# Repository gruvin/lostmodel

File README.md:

# Open Source RC Lost Model Alarm 
* Two modes -- Normal (manual switch) or Inactivity
* Modes programmable from TX 
* Resonated PIEZO
* LOUD!

Hardware design created in free, open source KiCAD EDA suite.

Employs ATmega88PA (5x5mm MLF) to intelligently drive a quartz piezo via autotransformer at 2.8KHz resonant frequency. This gives air and ear peircingly, LOUD output. Piezo and transformer taken from cheap personal alarm.

The circuit board is 16x33mm and the piezo is 28mm diameter and 3mm thick, including resonance chamber. The autotransformer (11mm height) can be mounted either on the top or bottom of the PCB or off board, if needed for space.

There are three status LEDs. Green, Blue and Red. They do, umm, stuff.

Programming and status tones are emitted (at lower, close range tolerable volume levels!) using Morse code, which I consider better than counting beeps for programming and status reporting.

The alarm can work in either Normal or Inactivity mode.

In Inactivity mode, ear peircing noise is made when there has been no receiver channel activity for a short while. Useful for cases where a dedicated RC channel is not available. Connect to aileron or elevator channel, for example.

Normal mode uses a dedicated receiver channel as a simple on/off switch. (Greater than or lower than mid point.)

## KiCAD v4 PCB Render

Autotransformer and off-board quartz piezo not shown.

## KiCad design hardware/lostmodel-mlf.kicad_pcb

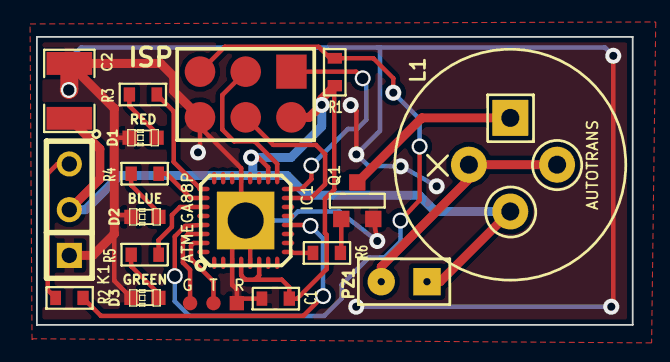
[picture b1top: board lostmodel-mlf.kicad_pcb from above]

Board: 2 copper layers, 33.1 x 16.0 mm, 18 parts (0 on the bottom side), 20 nets.

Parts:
C1: 0u1; SM0603_GRUVIN
C2: 22u; SM1210_GRUVIN_POL
D1: RED; LED-0603
D2: BLUE; LED-0603
D3: GREEN; LED-0603
IC1: ATMEGA88P; MLF-32_2mmVIA_SINK
K1: CONN_3; SIL-3
K2: G T R; TP-3
L1: AUTOTRANS; TRI-3
P1: ISP; PIN_ARRAY_3x2_GRUVIN
PZ1: PIEZO; PIN_ARRAY_2X1
Q1: BC847C; SOT23-BCE
R1: 5K6; SM0603_GRUVIN
R2: 200; SM0603_GRUVIN
R3, R6: 1K; SM0603_GRUVIN
R4: 3K9; SM0603_GRUVIN
R5: 1K5; SM0603_GRUVIN

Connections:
+5V: C1.1, C2.1, IC1.4, IC1.6, IC1.18, K1.2, L1.2, P1.2, PZ1.1, R1.1
/LED01: IC1.25, R3.2
/LED02: IC1.26, R4.2
/LED03: IC1.27, R5.2
/MISO: IC1.16, P1.1
/MOSI: IC1.15, P1.4
/RESET: IC1.29, P1.5, R1.2
/SCK: IC1.17, P1.3
/SIG: K1.3, R2.2
GND: C1.2, C2.2, D1.2, D2.2, D3.2, IC1.0, IC1.3, IC1.5, IC1.21, K1.1, K2.1, P1.6, Q1.2
unnamed: D1.1, R3.1
unnamed: D2.1, R4.1
unnamed: D3.1, R5.1
unnamed: IC1.9, R6.2
unnamed: IC1.12, R2.1
unnamed: IC1.30, K2.3
unnamed: IC1.31, K2.2
unnamed: L1.1, Q1.3
unnamed: L1.3, PZ1.2
unnamed: Q1.1, R6.1

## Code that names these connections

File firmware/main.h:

#ifndef _MAIN_H
#define _MAIN_H

#define DEBUG 1

// CW dit length (arbitrary units)
#define DITLENGTH 8 // arbitrary while morseStateMachine is just part of the main loop

// TODO: prototype version. Pins changed for production version ...
//       These are NOT the pins specified in the production electronic schematic
#define SIG_INP   PIND
#define SIG_PORT  PORTD
#define SIG_DDR   DDRD
#define SIG_BIT   3 // D-

#define PIEZO_PORT PORTD
#define PIEZO_DDR  DDRD
#define PIEZO_BIT  5 // LED01

#define LED1_PORT PORTC
#define LED1_DDR  DDRC
#define LED1_BIT  3 // LED05 (not used in prototype)

#define LED2_PORT PORTD
#define LED2_DDR  DDRD
#define LED2_BIT  4 // LED02

#define LED3_PORT PORTC
#define LED3_DDR  DDRC
#define LED3_BIT  5 // LED03

#define LED_ON(a) LED ## a ## _PORT |= (1<<LED ## a ## _BIT)
#define LED_OFF(a) LED ## a ## _PORT &= ~(1<<LED ## a ## _BIT)

#define MIDPOINT 1400 // timing loop should be exactly 10 clock cycles => 1200 loops for 1.5ms. 1400 works in practice. *shrug*

// PWM piezo output volume
#ifdef DEBUG
#define PWM_DUTY_CYCLE 3
#else
#define PWM_DUTY_CYCLE 27
#endif
#define PWM_DUTY_CYCLE_QUIET 2

#define true (-1)
#define false 0

// Run Modes
#define NORMAL 0
#define INACTIVITY 1



#endif

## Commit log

2014-11-24 Initial directory structure.
2014-11-24 Version 1.0 final
2014-11-24 r3 production files frozen
2014-11-25 pulseInWidth time-out counter improvements
2014-11-25 tweaks
2014-11-25 Better .lst file output
2014-11-25 Fixed the Makefile I broke -- I hope. Make is so damned confusing! :-(
2014-11-26 Finally sorted the broken Makefile out. Much better!
2014-11-26 object name changes and fixed compile options to give dissasembly for main() (objdump bug workaround)
2014-11-26 License.txt revised from GPLv2 to GPLv3.
2014-11-26 license notification text updated according to GPL guidelines.
2014-11-26 License text (again -- boring!) and some refactoring ... including putting the Morse state machine on a timer interrupt instead of the main loop.
2014-11-26 Getting ready for new PCBs and hardware pulse width counting using timer 1 ICP1(PB0) pin.
2014-11-27 Most TODOs completed.
2014-11-27 fixed WDT/BOR reset logic
2014-11-28 Backup before converting to hardware pulse timing
2014-11-28 Hardware pulse timing working. Inactivity mode and Program Mode system need re-working.
2014-11-28 Added UART break-out to PCB for possible future debug (or other) use.
2014-11-28 PCB v1.1 tidying after Gerber view check.
2014-11-30 Reduced morse table to 1/7th its former size, saving about 282 bytes of Flash.
    Changed "Normal/Inactivity Ready" (N/I R) to "Ready Normal,Inactivity" (R N/I) at start-up. *shrug*
2016-10-28 Revision v1.2 including KiCAD upgrade
2016-10-28 Added a KiCAD PCB render image
2016-10-28 Resolved README.md version mixup
2016-10-28 Completing KiCAD upgrade changes
